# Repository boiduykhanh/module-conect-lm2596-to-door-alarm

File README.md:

# module-conect-lm2596-to-door-alarm
## I. TỔNG QUAN  
  Module kết nối LM2596 với opto
 
## II. SƠ ĐỒ NGUYÊN LÝ

## Mạch in

## 3D

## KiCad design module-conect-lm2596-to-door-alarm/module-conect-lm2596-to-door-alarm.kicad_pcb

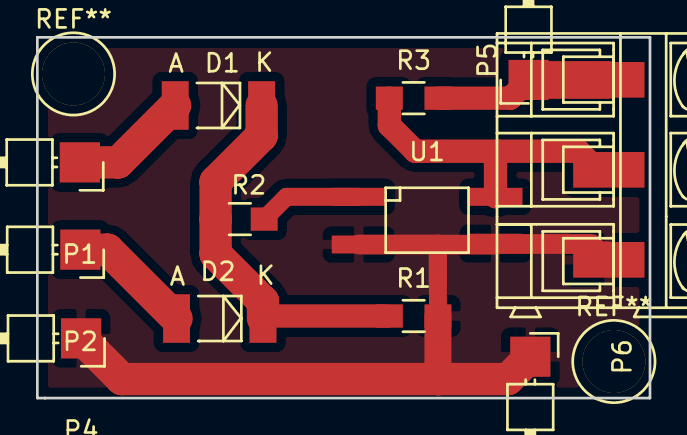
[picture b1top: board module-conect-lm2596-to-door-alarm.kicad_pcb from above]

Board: 2 copper layers, 34.0 x 20.0 mm, 12 parts (0 on the bottom side), 7 nets.

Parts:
D1, D2: M7; MELF_Standard
P1: IN1; Pin_Header_Angled_1x01
P2: IN2; Pin_Header_Angled_1x01
P3: CONN_01X03; AK300-3
P4: IN3; Pin_Header_Angled_1x01
P5: Vcc; Pin_Header_Angled_1x01
P6: GND; Pin_Header_Angled_1x01
R1, R3: 10K; R_0805_HandSoldering
R2: 2K2; R_0805_HandSoldering
U1: OPTO; Optocoupler_SMD_HandSoldering_KPC357_LTV35x_PC357_SingleCha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

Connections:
+12V: P3.1, P5.1, R3.2
GND: P3.3, P4.1, P6.1, R1.2, U1.2, U1.3
unnamed: D1.1, D2.1, R1.1, R2.2
unnamed: D1.2, P1.1
unnamed: D2.2, P2.1
unnamed: P3.2, R3.1, U1.4
unnamed: R2.1, U1.1

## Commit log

2016-06-17 initial module connect lm2596 to door alarm-kicad
2016-06-28 edit footring header
2016-07-15 module conect lm2596 to door alarm Version 1.1
